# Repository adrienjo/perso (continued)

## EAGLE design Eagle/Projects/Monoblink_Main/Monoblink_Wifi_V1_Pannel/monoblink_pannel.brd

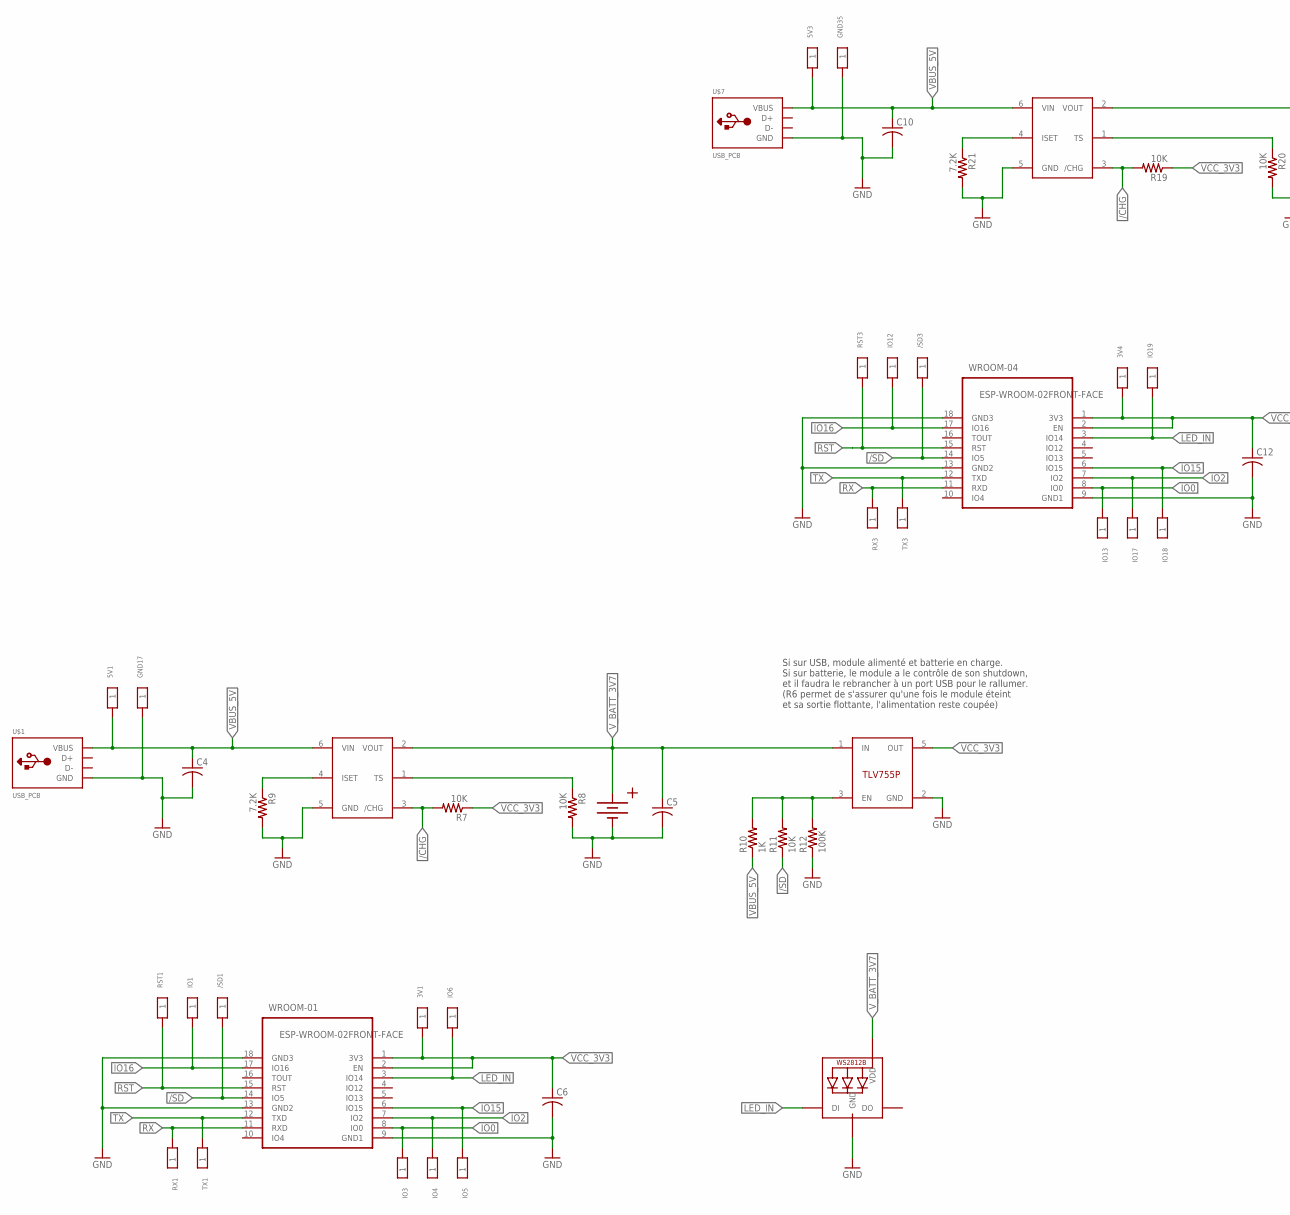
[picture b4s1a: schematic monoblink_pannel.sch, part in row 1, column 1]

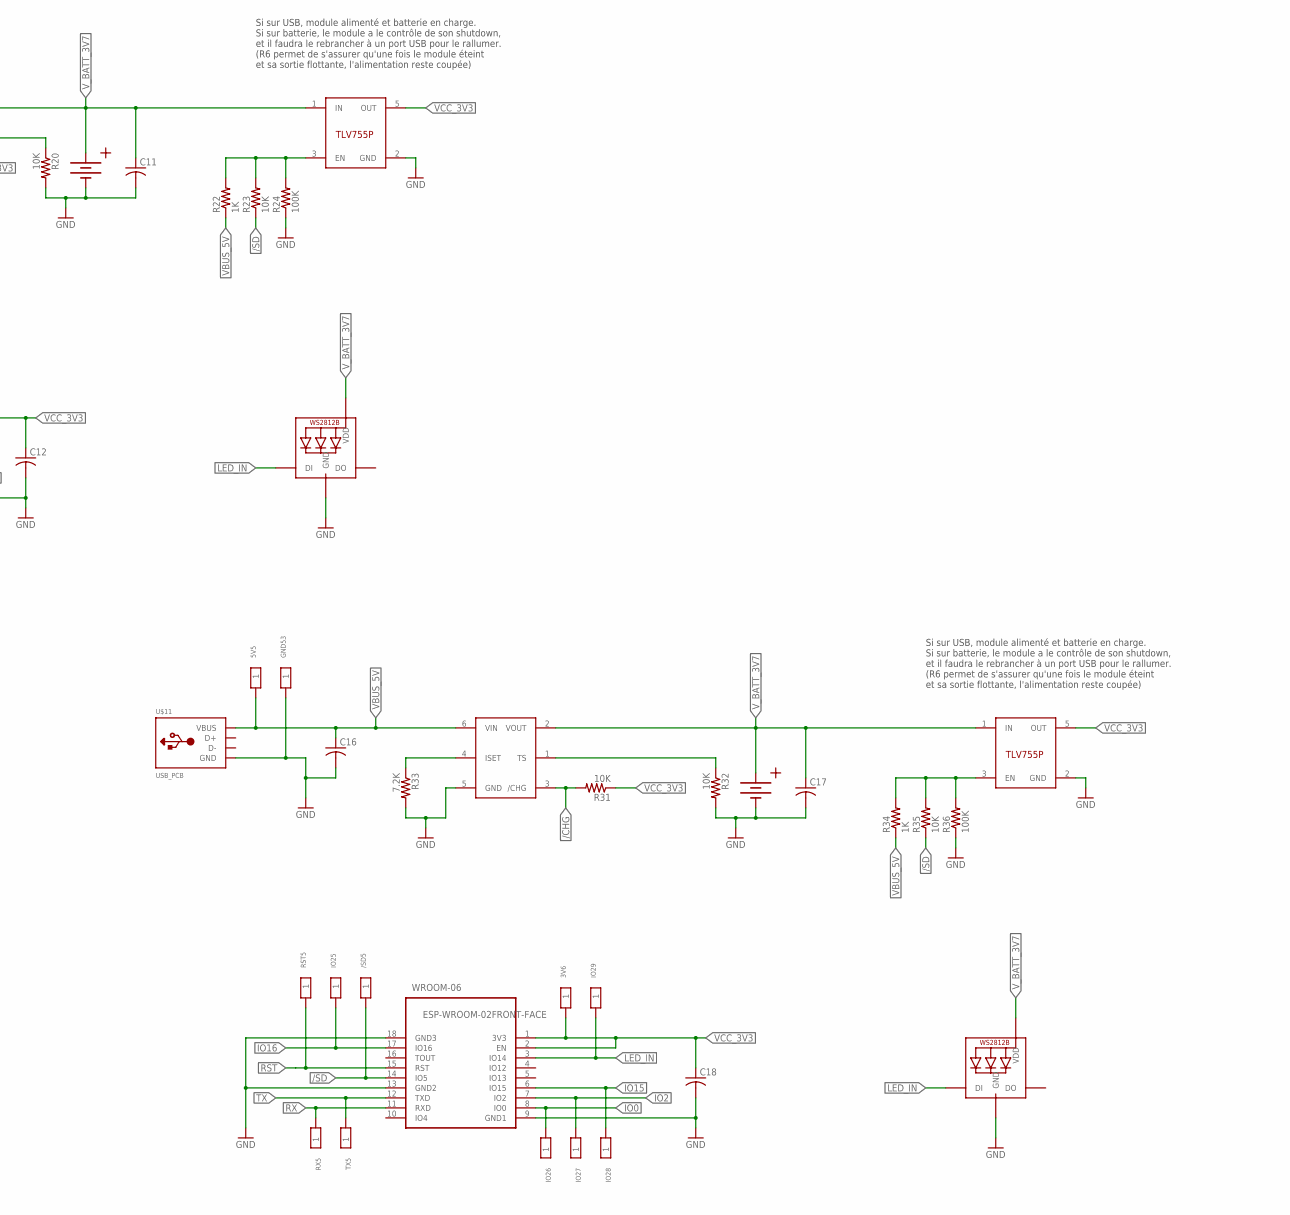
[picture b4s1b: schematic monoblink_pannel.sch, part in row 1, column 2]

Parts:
3V1, 3V4, 3V6, 5V1, 5V3, 5V5: TESTPAD_PROG; TP1.5MM
/SD1, /SD3, /SD5: TESTPAD_PROG; TP1.5MM
C4, C5, C6, C10, C11, C12, C16, C17, C18: C-USC0603; C0603
CHG1, CHG3, CHG5: BQ21040; SOT23-6
GND17, GND35, GND53: TESTPAD_PROG; TP1.5MM
IO1, IO3, IO4, IO5, IO6, IO12, IO13, IO17, IO18, IO19, IO25, IO26, IO27, IO28, IO29: TESTPAD_PROG; TP1.5MM
LDO1, LDO3, LDO5: TLV755P; SOT23-5
LED1, LED3, LED5: WS2812B5050; WS2812B
R7, R8, R11, R19, R20, R23, R31, R32, R35: 10K; R0603
R9, R21, R33: 7.2K; R0603
R10, R22, R34: 1K; R0603
R12, R24, R36: 100K; R0603
RST1, RST3, RST5: TESTPAD_PROG; TP1.5MM
RX1, RX3, RX5: TESTPAD_PROG; TP1.5MM
TX1, TX3, TX5: TESTPAD_PROG; TP1.5MM
U$1, U$7, U$11: USB_PCB; USB_PADS
U$3, U$8, U$12: BATT; BATT_CON
WROOM-01, WROOM-04, WROOM-06: ESP-WROOM-02FRONT-FACE; FRONT-FACE

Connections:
/CHG: CHG1.3 (/CHG), CHG3.3 (/CHG), CHG5.3 (/CHG), R7.2, R19.2, R31.2
/SD: /SD1.1, /SD3.1, /SD5.1, R11.1, R23.1, R35.1, WROOM-01.14 (IO5), WROOM-04.14 (IO5), WROOM-06.14 (IO5)
EN1: LDO1.3 (EN), R10.2, R11.2, R12.2
EN3: LDO3.3 (EN), R22.2, R23.2, R24.2
EN5: LDO5.3 (EN), R34.2, R35.2, R36.2
GND: C4.2, C5.2, C6.2, C10.2, C11.2, C12.2, C16.2, C17.2, C18.2, CHG1.5 (GND), CHG3.5 (GND), CHG5.5 (GND), GND17.1, GND35.1, GND53.1, LDO1.2 (GND), LDO3.2 (GND), LDO5.2 (GND), LED1.3-GND (GND), LED3.3-GND (GND), LED5.3-GND (GND), R8.2, R9.2, R12.1, R20.2, R21.2, R24.1, R32.2, R33.2, R36.1, U$1.GND, U$3.V- (-), U$7.GND, U$8.V- (-), U$11.GND, U$12.V- (-), WROOM-01.9 (GND1), WROOM-01.13 (GND2), WROOM-01.18 (GND3), WROOM-04.9 (GND1), WROOM-04.13 (GND2), WROOM-04.18 (GND3), WROOM-06.9 (GND1), WROOM-06.13 (GND2), WROOM-06.18 (GND3)
IO0: IO3.1, IO13.1, IO26.1, WROOM-01.8 (IO0), WROOM-04.8 (IO0), WROOM-06.8 (IO0)
IO2: IO4.1, IO17.1, IO27.1, WROOM-01.7 (IO2), WROOM-04.7 (IO2), WROOM-06.7 (IO2)
IO15: IO5.1, IO18.1, IO28.1, WROOM-01.6 (IO15), WROOM-04.6 (IO15), WROOM-06.6 (IO15)
IO16: IO1.1, IO12.1, IO25.1, WROOM-01.17 (IO16), WROOM-04.17 (IO16), WROOM-06.17 (IO16)
ISET1: CHG1.4 (ISET), R9.1
ISET3: CHG3.4 (ISET), R21.1
ISET5: CHG5.4 (ISET), R33.1
LED_IN: IO6.1, IO19.1, IO29.1, LED1.4-DIN (DI), LED3.4-DIN (DI), LED5.4-DIN (DI), WROOM-01.3 (IO14), WROOM-04.3 (IO14), WROOM-06.3 (IO14)
RST: RST1.1, RST3.1, RST5.1, WROOM-01.15 (RST), WROOM-04.15 (RST), WROOM-06.15 (RST)
RX: RX1.1, RX3.1, RX5.1, WROOM-01.11 (RXD), WROOM-04.11 (RXD), WROOM-06.11 (RXD)
TS1: CHG1.1 (TS), R8.1
TS3: CHG3.1 (TS), R20.1
TS5: CHG5.1 (TS), R32.1
TX: TX1.1, TX3.1, TX5.1, WROOM-01.12 (TXD), WROOM-04.12 (TXD), WROOM-06.12 (TXD)
VBUS_5V: 5V1.1, 5V3.1, 5V5.1, C4.1, C10.1, C16.1, CHG1.6 (VIN), CHG3.6 (VIN), CHG5.6 (VIN), R10.1, R22.1, R34.1, U$1.V_SUPPLY (VBUS), U$7.V_SUPPLY (VBUS), U$11.V_SUPPLY (VBUS)
VCC_3V3: 3V1.1, 3V4.1, 3V6.1, C6.1, C12.1, C18.1, LDO1.5 (OUT), LDO3.5 (OUT), LDO5.5 (OUT), R7.1, R19.1, R31.1, WROOM-01.1 (3V3), WROOM-01.2 (EN), WROOM-04.1 (3V3), WROOM-04.2 (EN), WROOM-06.1 (3V3), WROOM-06.2 (EN)
V_BATT_3V7: C5.1, C11.1, C17.1, CHG1.2 (VOUT), CHG3.2 (VOUT), CHG5.2 (VOUT), LDO1.1 (IN), LDO3.1 (IN), LDO5.1 (IN), LED1.1-VDD (VDD), LED3.1-VDD (VDD), LED5.1-VDD (VDD), U$3.V+ (+), U$8.V+ (+), U$12.V+ (+)

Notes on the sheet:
Si sur USB, module alimenté et batterie en charge. Si sur batterie, le module a le contrôle de son shutdown, et il faudra le rebrancher à un port USB pour le rallumer. (R6 permet de s'assurer qu'une fois le module éteint et sa sortie flottante, l'alimentation reste coupée)

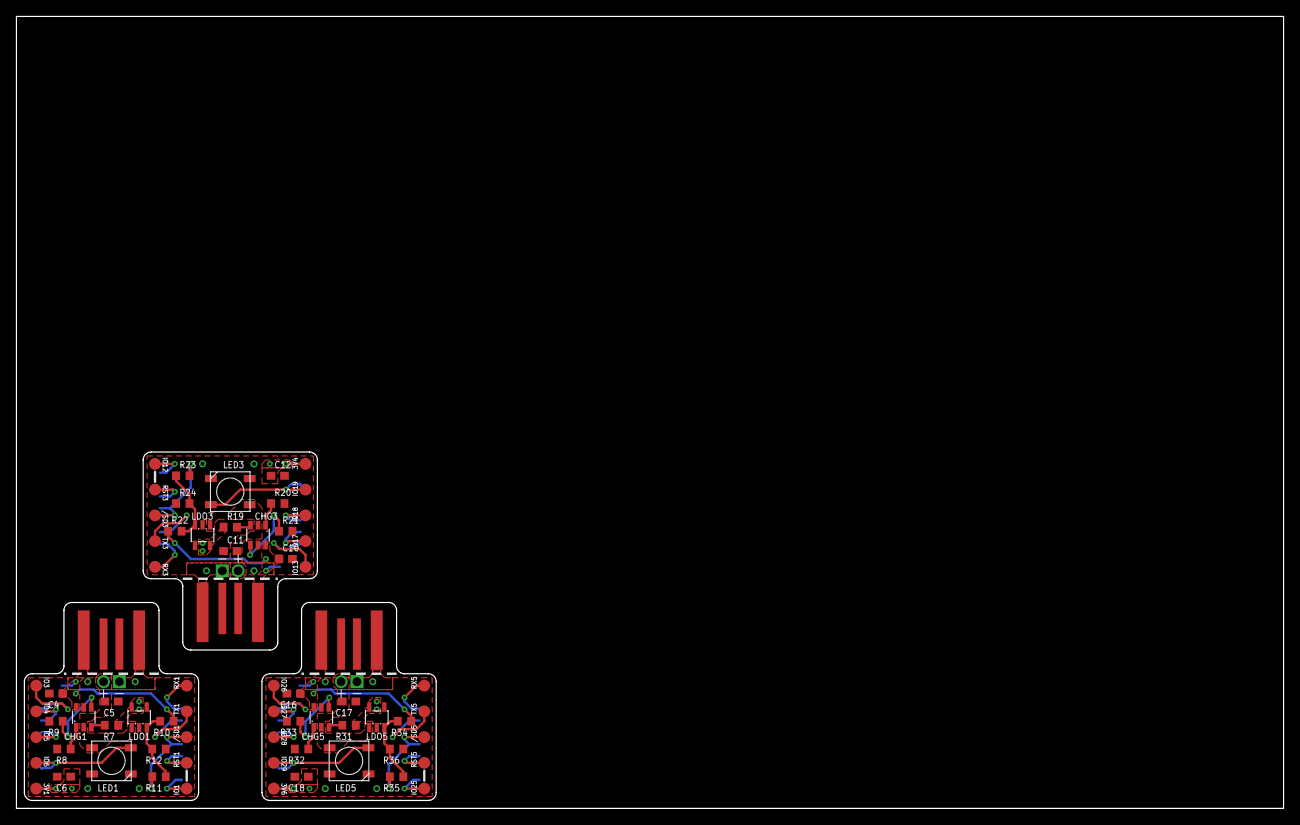
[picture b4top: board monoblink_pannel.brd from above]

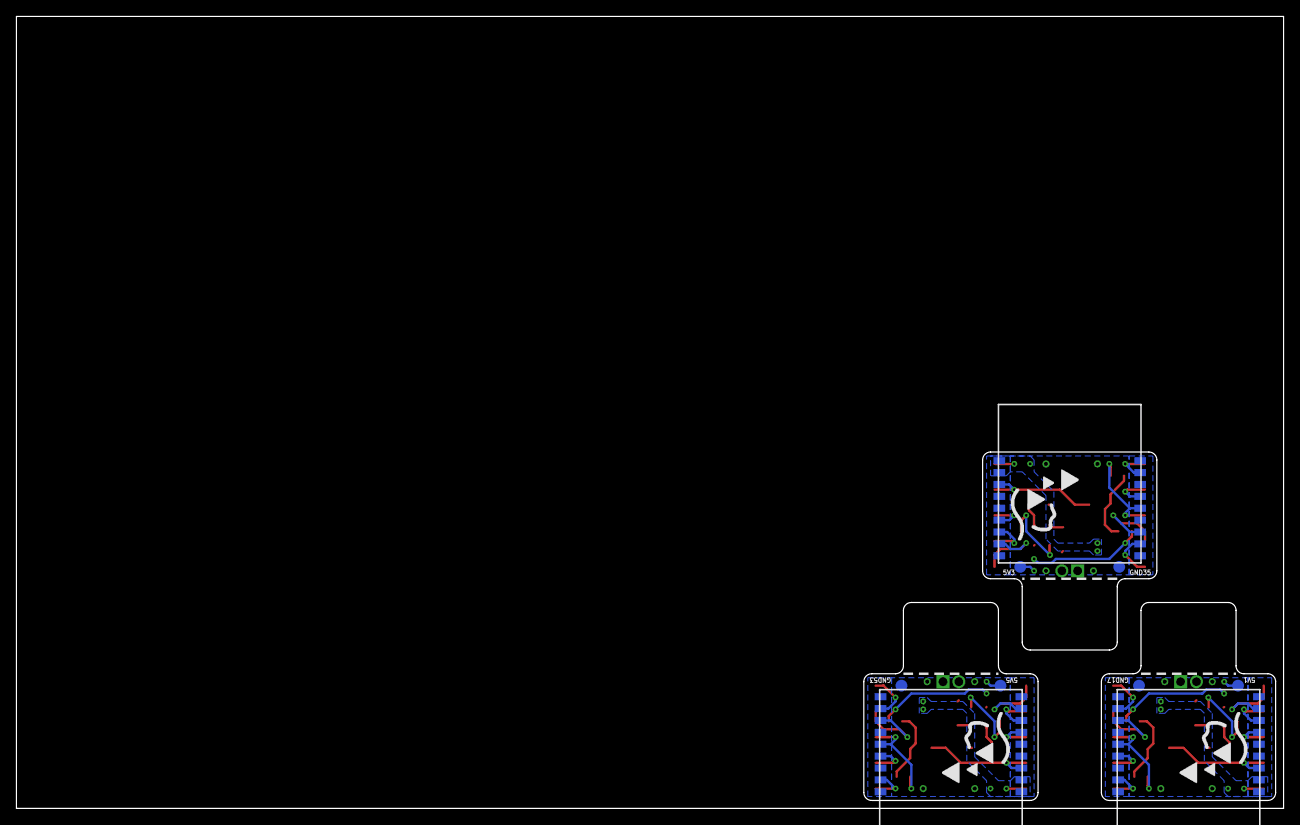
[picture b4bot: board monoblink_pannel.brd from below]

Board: 2 copper layers, 160.0 x 100.0 mm, 81 parts (9 on the bottom side), 23 nets.

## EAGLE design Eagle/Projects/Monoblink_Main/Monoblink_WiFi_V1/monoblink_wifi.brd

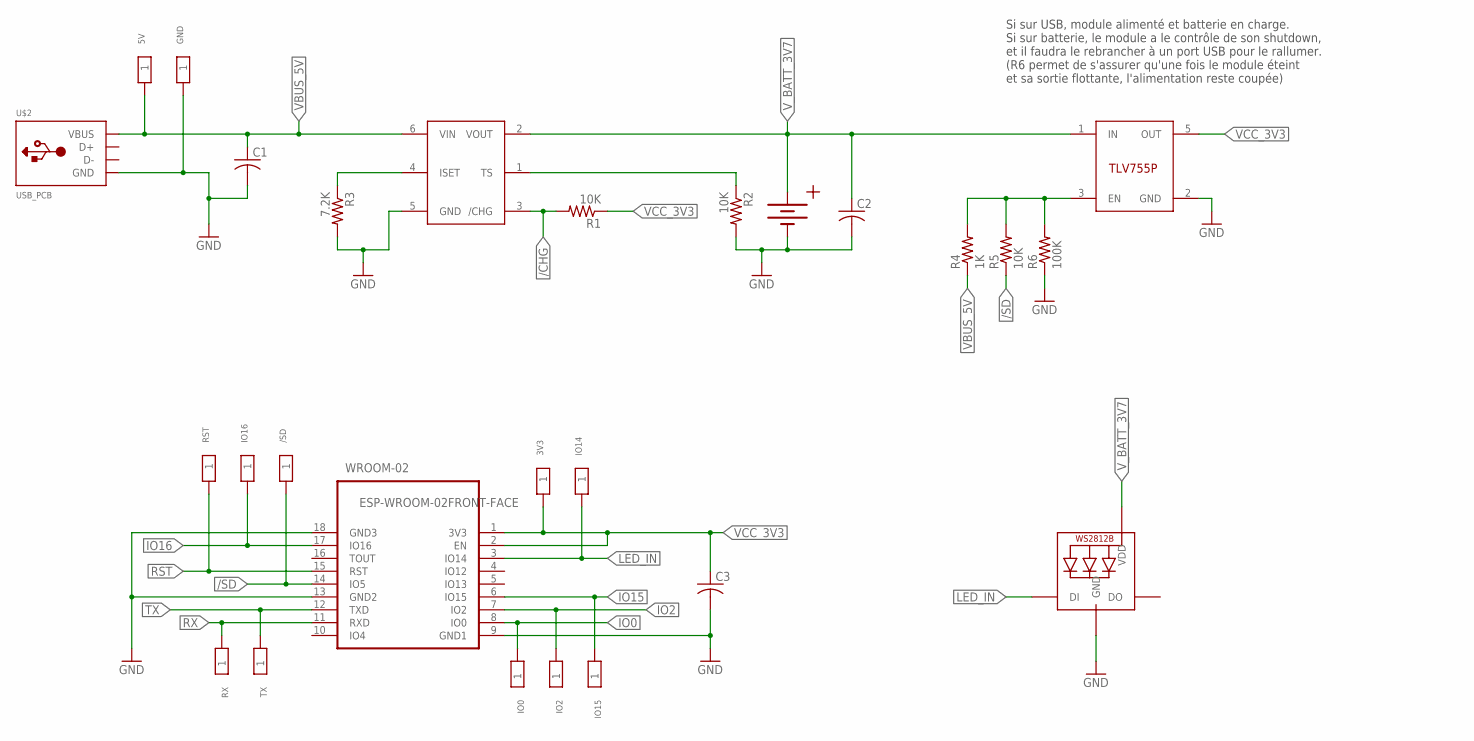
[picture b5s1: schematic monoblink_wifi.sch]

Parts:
3V3, 5V: TESTPAD_PROG; TP1.5MM
/SD: TESTPAD_PROG; TP1.5MM
C1, C2, C3: C-USC0603; C0603
CHG: BQ21040; SOT23-6
GND: TESTPAD_PROG; TP1.5MM
IO0, IO2, IO14, IO15, IO16: TESTPAD_PROG; TP1.5MM
LDO: TLV755P; SOT23-5
LED: WS2812B5050; WS2812B
R1, R2, R5: 10K; R0603
R3: 7.2K; R0603
R4: 1K; R0603
R6: 100K; R0603
RST: TESTPAD_PROG; TP1.5MM
RX: TESTPAD_PROG; TP1.5MM
TX: TESTPAD_PROG; TP1.5MM
U$2: USB_PCB; USB_PADS
U$5: BATT; BATT_CON
WROOM-02: ESP-WROOM-02FRONT-FACE; FRONT-FACE

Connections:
/CHG: CHG.3 (/CHG), R1.2
/SD: /SD.1, R5.1, WROOM-02.14 (IO5)
EN: LDO.3 (EN), R4.2, R5.2, R6.2
GND: C1.2, C2.2, C3.2, CHG.5 (GND), GND.1, LDO.2 (GND), LED.3-GND (GND), R2.2, R3.2, R6.1, U$2.GND, U$5.V- (-), WROOM-02.9 (GND1), WROOM-02.13 (GND2), WROOM-02.18 (GND3)
IO0: IO0.1, WROOM-02.8 (IO0)
IO2: IO2.1, WROOM-02.7 (IO2)
IO15: IO15.1, WROOM-02.6 (IO15)
IO16: IO16.1, WROOM-02.17 (IO16)
ISET: CHG.4 (ISET), R3.1
LED_IN: IO14.1, LED.4-DIN (DI), WROOM-02.3 (IO14)
RST: RST.1, WROOM-02.15 (RST)
RX: RX.1, WROOM-02.11 (RXD)
TS: CHG.1 (TS), R2.1
TX: TX.1, WROOM-02.12 (TXD)
VBUS_5V: 5V.1, C1.1, CHG.6 (VIN), R4.1, U$2.V_SUPPLY (VBUS)
VCC_3V3: 3V3.1, C3.1, LDO.5 (OUT), R1.1, WROOM-02.1 (3V3), WROOM-02.2 (EN)
V_BATT_3V7: C2.1, CHG.2 (VOUT), LDO.1 (IN), LED.1-VDD (VDD), U$5.V+ (+)

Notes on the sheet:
Si sur USB, module alimenté et batterie en charge. Si sur batterie, le module a le contrôle de son shutdown, et il faudra le rebrancher à un port USB pour le rallumer. (R6 permet de s'assurer qu'une fois le module éteint et sa sortie flottante, l'alimentation reste coupée)

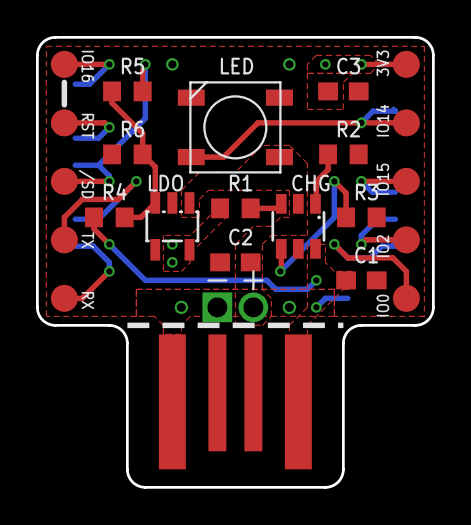
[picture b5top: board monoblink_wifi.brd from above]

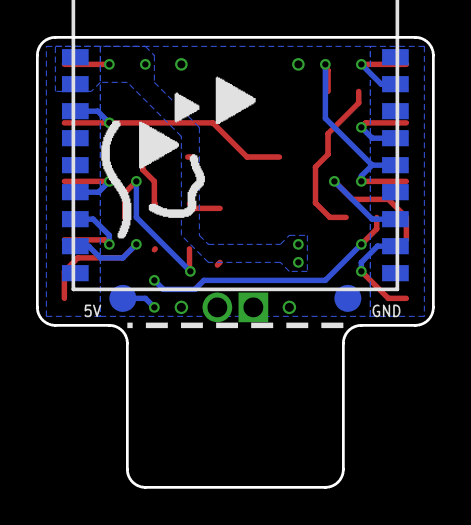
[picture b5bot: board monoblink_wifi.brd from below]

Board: 2 copper layers, 22.0 x 25.0 mm, 27 parts (3 on the bottom side), 17 nets.

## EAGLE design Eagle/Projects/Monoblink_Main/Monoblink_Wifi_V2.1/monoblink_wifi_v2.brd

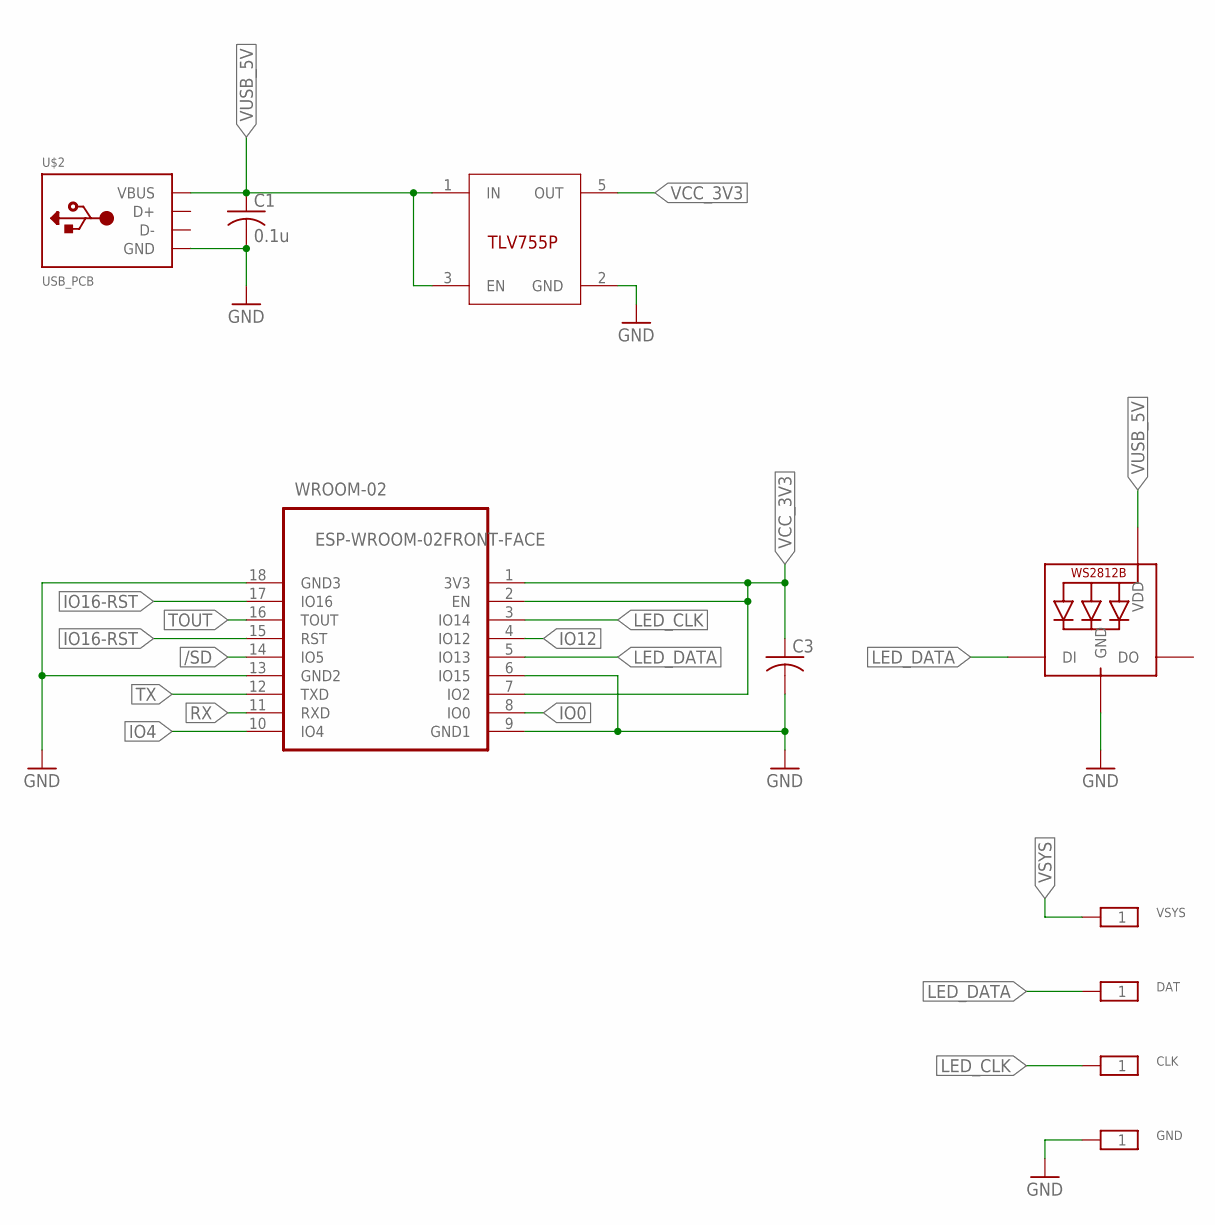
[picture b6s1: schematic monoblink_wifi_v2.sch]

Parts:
C1: 0.1u; C0603
C3: C-USC0603; C0603
CLK: TESTPAD_PROG; TP1.5MM
DAT: TESTPAD_PROG; TP1.5MM
GND: TESTPAD_PROG; TP1.5MM
LDO: TLV755P; SOT23-5
LED: WS2812B5050; WS2812B
U$2: USB_PCB; USB_PADS
VSYS: TESTPAD_PROG; TP1.5MM
WROOM-02: ESP-WROOM-02FRONT-FACE; FRONT-FACE

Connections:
/SD: WROOM-02.14 (IO5)
GND: C1.2, C3.2, GND.1, LDO.2 (GND), LED.3-GND (GND), U$2.GND, WROOM-02.6 (IO15), WROOM-02.9 (GND1), WROOM-02.13 (GND2), WROOM-02.18 (GND3)
IO0: WROOM-02.8 (IO0)
IO4: WROOM-02.10 (IO4)
IO12: WROOM-02.4 (IO12)
IO16-RST: WROOM-02.15 (RST), WROOM-02.17 (IO16)
LED_CLK: CLK.1, WROOM-02.3 (IO14)
LED_DATA: DAT.1, LED.4-DIN (DI), WROOM-02.5 (IO13)
RX: WROOM-02.11 (RXD)
TOUT: WROOM-02.16 (TOUT)
TX: WROOM-02.12 (TXD)
VCC_3V3: C3.1, LDO.5 (OUT), WROOM-02.1 (3V3), WROOM-02.2 (EN), WROOM-02.7 (IO2)
VSYS: VSYS.1
VUSB_5V: C1.1, LDO.1 (IN), LDO.3 (EN), LED.1-VDD (VDD), U$2.V_SUPPLY (VBUS)

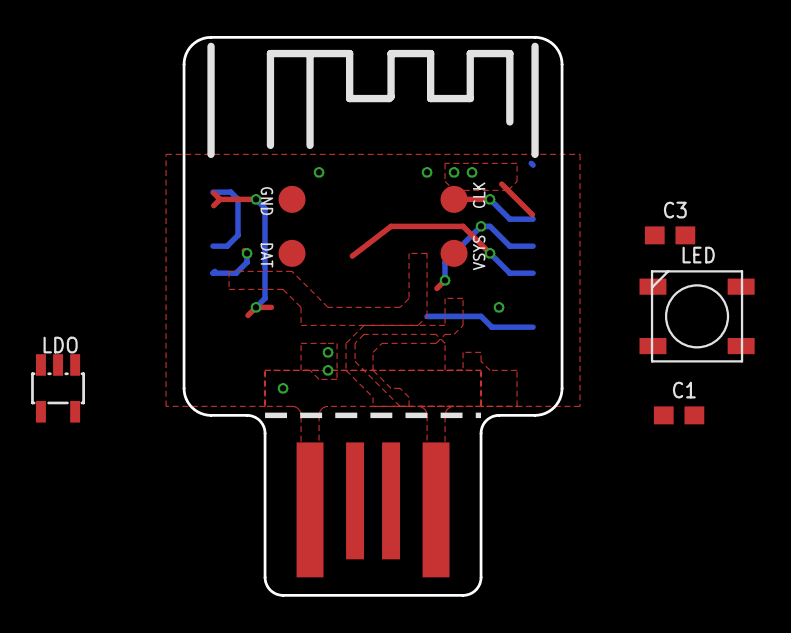
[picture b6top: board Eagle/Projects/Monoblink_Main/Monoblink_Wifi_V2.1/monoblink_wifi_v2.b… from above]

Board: 2 copper layers, 21.0 x 31.0 mm, 10 parts (1 on the bottom side), 6 nets.

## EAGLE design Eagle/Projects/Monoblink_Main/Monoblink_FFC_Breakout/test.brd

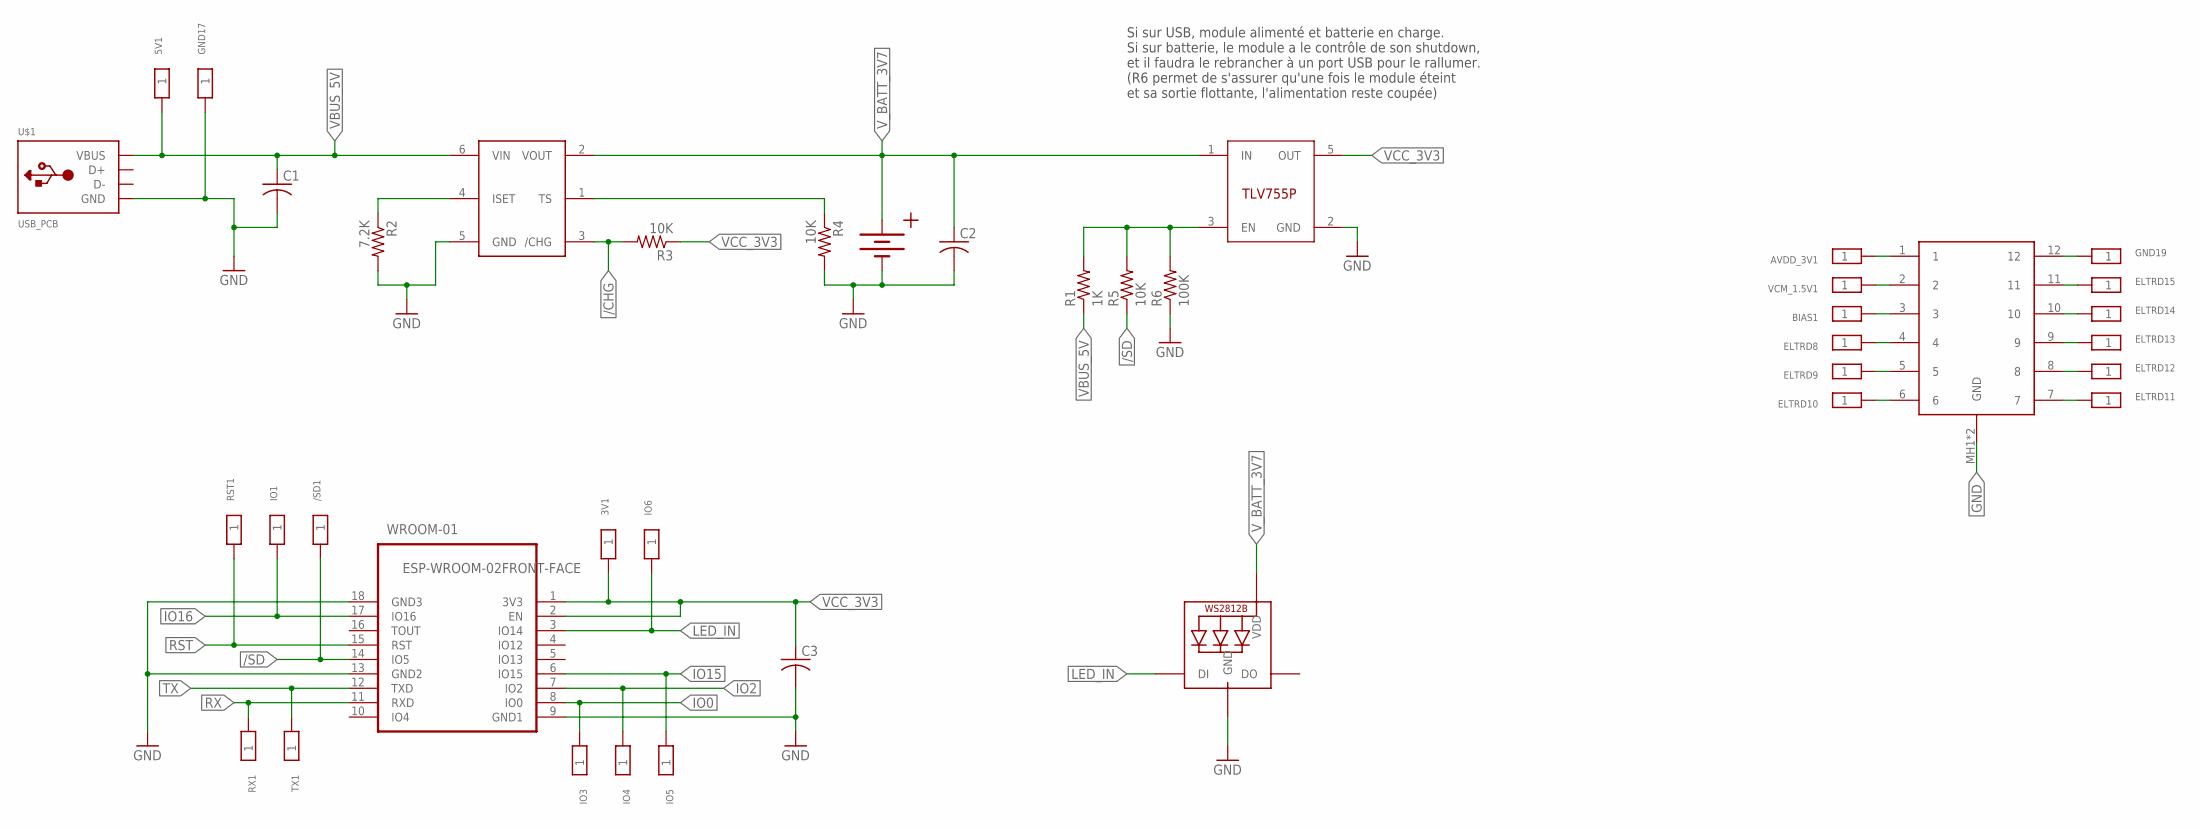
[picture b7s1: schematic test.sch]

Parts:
3V1, 5V1: TESTPAD_PROG; TP1.5MM
/SD1: TESTPAD_PROG; TP1.5MM
AVDD_3V1: TESTPAD_PROG; TP1.5MM
BIAS1: TESTPAD_PROG; TP1.5MM
C1, C2, C3: C-USC0603; C0603
CHG1: BQ21040; SOT23-6
CONN1: 505110-1292
ELTRD8, ELTRD9, ELTRD10, ELTRD11, ELTRD12, ELTRD13, ELTRD14, ELTRD15: TESTPAD_PROG; TP1.5MM
GND17, GND19: TESTPAD_PROG; TP1.5MM
IO1, IO3, IO4, IO5, IO6: TESTPAD_PROG; TP1.5MM
LDO1: TLV755P; SOT23-5
LED1: WS2812B5050; WS2812B
R1: 1K; R0603
R2: 7.2K; R0603
R3, R4, R5: 10K; R0603
R6: 100K; R0603
RST1: TESTPAD_PROG; TP1.5MM
RX1: TESTPAD_PROG; TP1.5MM
TX1: TESTPAD_PROG; TP1.5MM
U$1: USB_PCB; USB_PADS
U$3: BATT; BATT_CON
VCM_1.5V1: TESTPAD_PROG; TP1.5MM
WROOM-01: ESP-WROOM-02FRONT-FACE; FRONT-FACE

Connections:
/CHG: CHG1.3 (/CHG), R3.2
/SD: /SD1.1, R5.1, WROOM-01.14 (IO5)
AVDD_3V1: AVDD_3V1.1, CONN1.1
BIAS1: BIAS1.1, CONN1.3
ELTRD8: CONN1.4, ELTRD8.1
ELTRD9: CONN1.5, ELTRD9.1
ELTRD10: CONN1.6, ELTRD10.1
ELTRD11: CONN1.7, ELTRD11.1
ELTRD12: CONN1.8, ELTRD12.1
ELTRD13: CONN1.9, ELTRD13.1
ELTRD14: CONN1.10, ELTRD14.1
ELTRD15: CONN1.11, ELTRD15.1
EN1: LDO1.3 (EN), R1.2, R5.2, R6.2
GND: C1.2, C2.2, C3.2, CHG1.5 (GND), CONN1.MH1 (GND), CONN1.MH2 (GND), GND17.1, LDO1.2 (GND), LED1.3-GND (GND), R2.2, R4.2, R6.1, U$1.GND, U$3.V- (-), WROOM-01.9 (GND1), WROOM-01.13 (GND2), WROOM-01.18 (GND3)
IO0: IO3.1, WROOM-01.8 (IO0)
IO2: IO4.1, WROOM-01.7 (IO2)
IO15: IO5.1, WROOM-01.6 (IO15)
IO16: IO1.1, WROOM-01.17 (IO16)
ISET1: CHG1.4 (ISET), R2.1
LED_IN: IO6.1, LED1.4-DIN (DI), WROOM-01.3 (IO14)
unnamed: CONN1.12, GND19.1
RST: RST1.1, WROOM-01.15 (RST)
RX: RX1.1, WROOM-01.11 (RXD)
TS1: CHG1.1 (TS), R4.1
TX: TX1.1, WROOM-01.12 (TXD)
VBUS_5V: 5V1.1, C1.1, CHG1.6 (VIN), R1.1, U$1.V_SUPPLY (VBUS)
VCC_3V3: 3V1.1, C3.1, LDO1.5 (OUT), R3.1, WROOM-01.1 (3V3), WROOM-01.2 (EN)
VCM_1.5V1: CONN1.2, VCM_1.5V1.1
V_BATT_3V7: C2.1, CHG1.2 (VOUT), LDO1.1 (IN), LED1.1-VDD (VDD), U$3.V+ (+)

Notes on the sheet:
Si sur USB, module alimenté et batterie en charge. Si sur batterie, le module a le contrôle de son shutdown, et il faudra le rebrancher à un port USB pour le rallumer. (R6 permet de s'assurer qu'une fois le module éteint et sa sortie flottante, l'alimentation reste coupée)

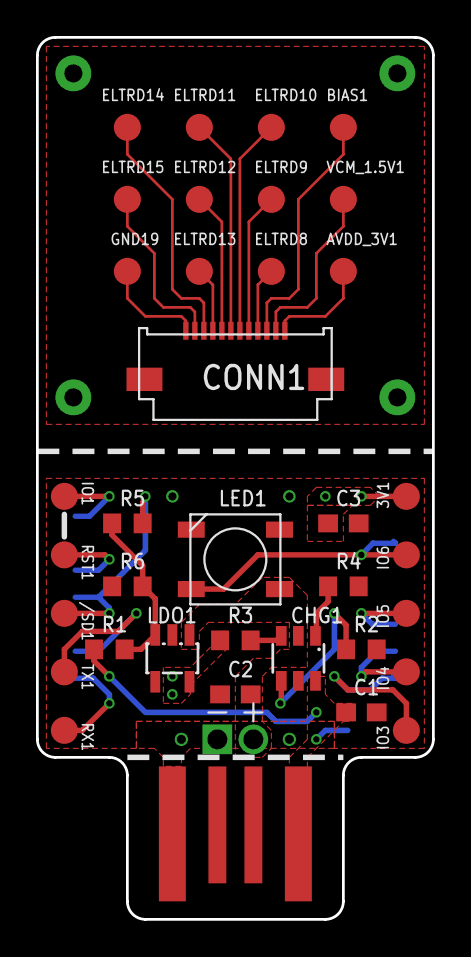
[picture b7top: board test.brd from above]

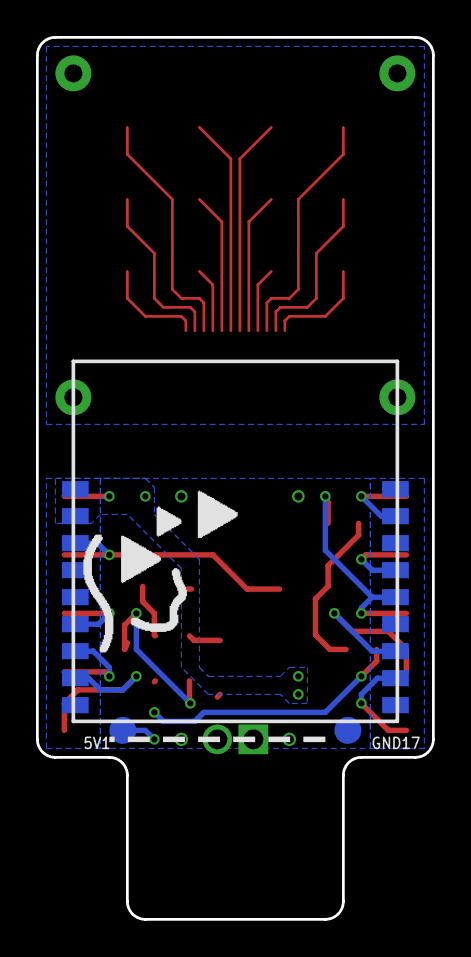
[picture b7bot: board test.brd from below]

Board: 2 copper layers, 22.0 x 49.0 mm, 40 parts (3 on the bottom side), 29 nets.

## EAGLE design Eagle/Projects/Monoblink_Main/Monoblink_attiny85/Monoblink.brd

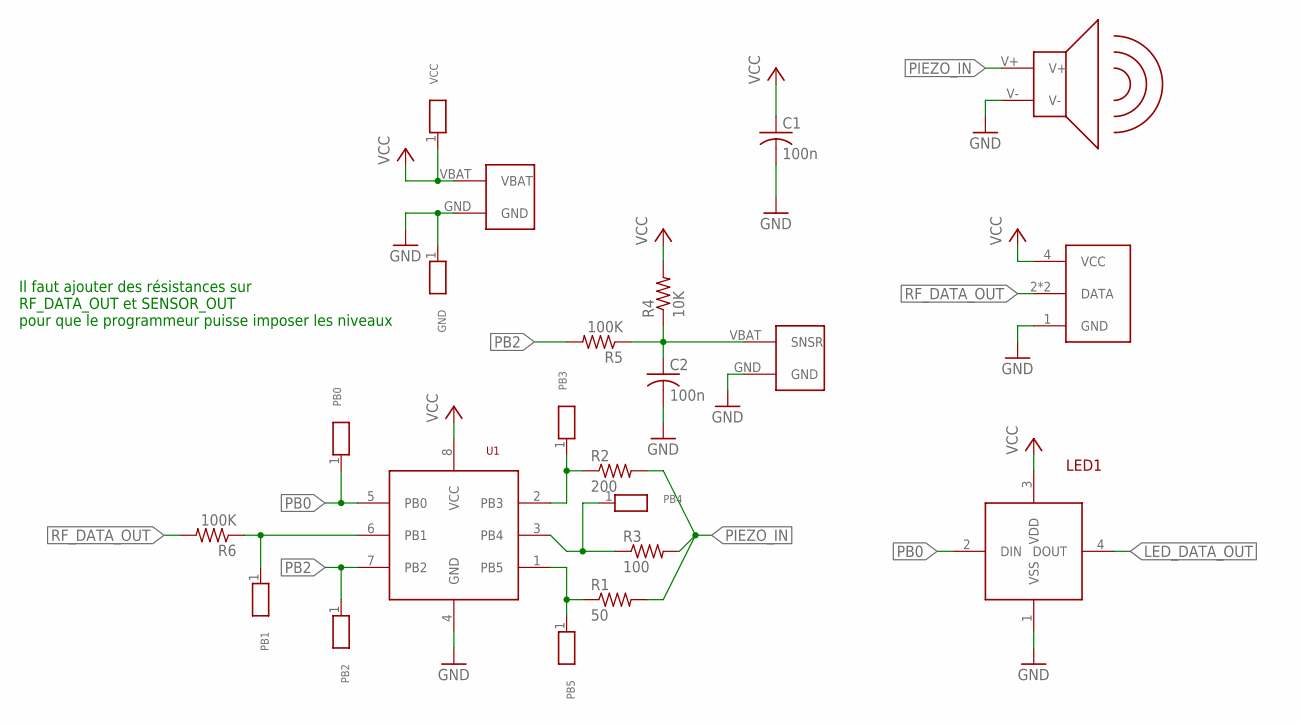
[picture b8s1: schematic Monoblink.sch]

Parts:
C1, C2: 100n; C0603
GND: TESTPAD_PROG_BOARD; TP2MM
LED1: NEOPIXEL; SMD5050
PB0, PB1, PB2, PB3, PB4, PB5: TESTPAD_PROG_BOARD; TP2MM
R1: 50; R0603
R2: 200; R0603
R3: 100; R0603
R4: 10K; R0603
R5, R6: 100K; R0603
U1: ATTINY85; SOIC8
U$1: RF_CONN
U$2: PIEZO; PS1240P02BT
U$3: BATT_TH; TWO_TH
U$4: SNSR_CONN; TWO_TH
VCC: TESTPAD_PROG_BOARD; TP2MM

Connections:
GND: C1.2, C2.2, GND.1, LED1.1 (VSS), U1.4 (GND), U$1.1 (GND), U$2.V-, U$3.GND, U$4.GND
LED_DATA_OUT: LED1.4 (DOUT)
PB0: LED1.2 (DIN), PB0.1, U1.5 (PB0)
PB1: PB1.1, R6.1, U1.6 (PB1)
PB2: PB2.1, R5.2, U1.7 (PB2)
PB3: PB3.1, R2.1, U1.2 (PB3)
PB4: PB4.1, R3.1, U1.3 (PB4)
PB5: PB5.1, R1.1, U1.1 (PB5)
PIEZO_IN: R1.2, R2.2, R3.2, U$2.V+
RF_DATA_OUT: R6.2, U$1.2 (DATA), U$1.3 (DATA)
SENSOR_OUT: C2.1, R4.1, R5.1, U$4.VBAT (SNSR)
VCC: C1.1, LED1.3 (VDD), R4.2, U1.8 (VCC), U$1.4 (VCC), U$3.VBAT, VCC.1

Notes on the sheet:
Il faut ajouter des résistances sur RF_DATA_OUT et SENSOR_OUT pour que le programmeur puisse imposer les niveaux

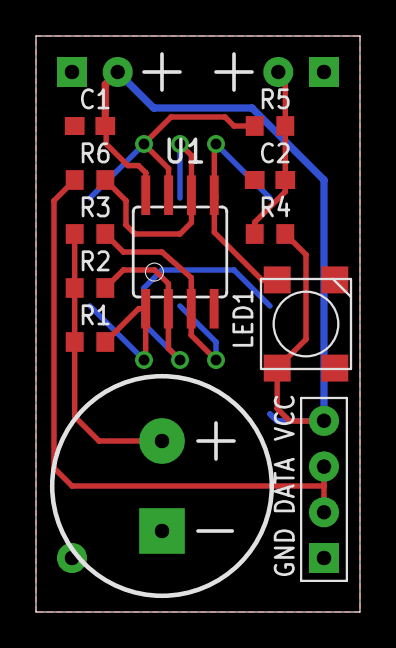
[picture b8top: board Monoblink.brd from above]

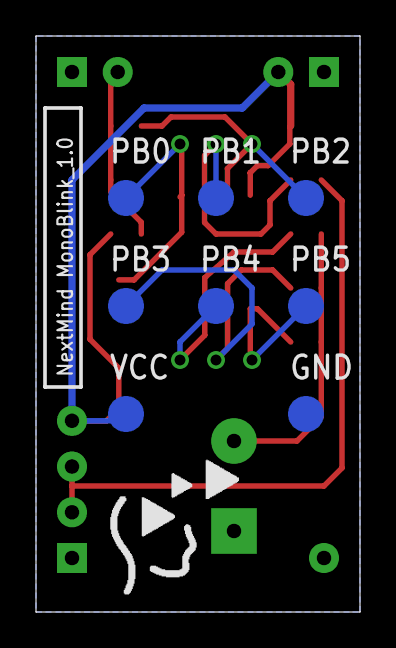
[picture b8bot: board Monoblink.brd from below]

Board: 2 copper layers, 18.0 x 32.0 mm, 22 parts (8 on the bottom side), 11 nets.

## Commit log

2018-01-14 ebauche projet neopixel propre
2018-01-14 continu
2018-01-15 pointeur sur Strip
2018-01-15 classes vibreur et sensor
2018-01-16 monoblink
2018-01-16 monoblink filenames
2018-01-16 trucs virés
2018-01-21 timer0 initialisé pour pwm vibreurs
2018-02-01 bleurble
2018-02-01 rebleuble
2018-09-27 electrode tester + fichiers cam et dru
2018-10-01 3d models + monoblink_clean
2018-10-04 monoblink main
2018-10-04 rerg
2018-10-04 zrzg
2018-10-04 monoblink lib
2018-10-05 dio commander
2018-10-05 dio_commander added
2018-11-05 git update
2018-11-05 delete_library_backup
